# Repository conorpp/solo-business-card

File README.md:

# solo-business-card
A flex PCB business card that also works as a Solo

# BOM

|  Ref | value  | type  | package  | quantity  | Required? |
|---|---|---|---|---|--|
| C1-C9,C11  | 4.7u  | capacitor  | 0402  | 10  | yes |
| C10,C12  | \* xx, yy  | C0G capacitor  | 0402  | 10  | yes |
|  ST1 | STM32L432KU  |  Microcontroller | QFN32  | 1  |yes |
| N1  | AS3956-ATDM-S4  | NFC IC (SPI version)  | MLPD 3x3  | 1  |  yes |
|  R1 | 500R  | resistor  | 0402  | 1  |  no |
|  L1 | CL-505S-X-SD-T  | RGB LED  | 0606  | 1  |  no |

\* C10 and C12 are tunning capacitors connected in parallel.  I have not yet measured what the nominal value for them should be, but will be somewhere around 45pF.

# Assembly instructions

Assemble BOM on badge. 

# Programming

Connect programmer to debug port.  Connector uses the following cable.

http://www.tag-connect.com/TC2030-CTX-NL

Connect cable to an ARM debugger/programmer.  And program one of the "bundle" builds from the latest Solo release.

https://github.com/solokeys/solo/releases

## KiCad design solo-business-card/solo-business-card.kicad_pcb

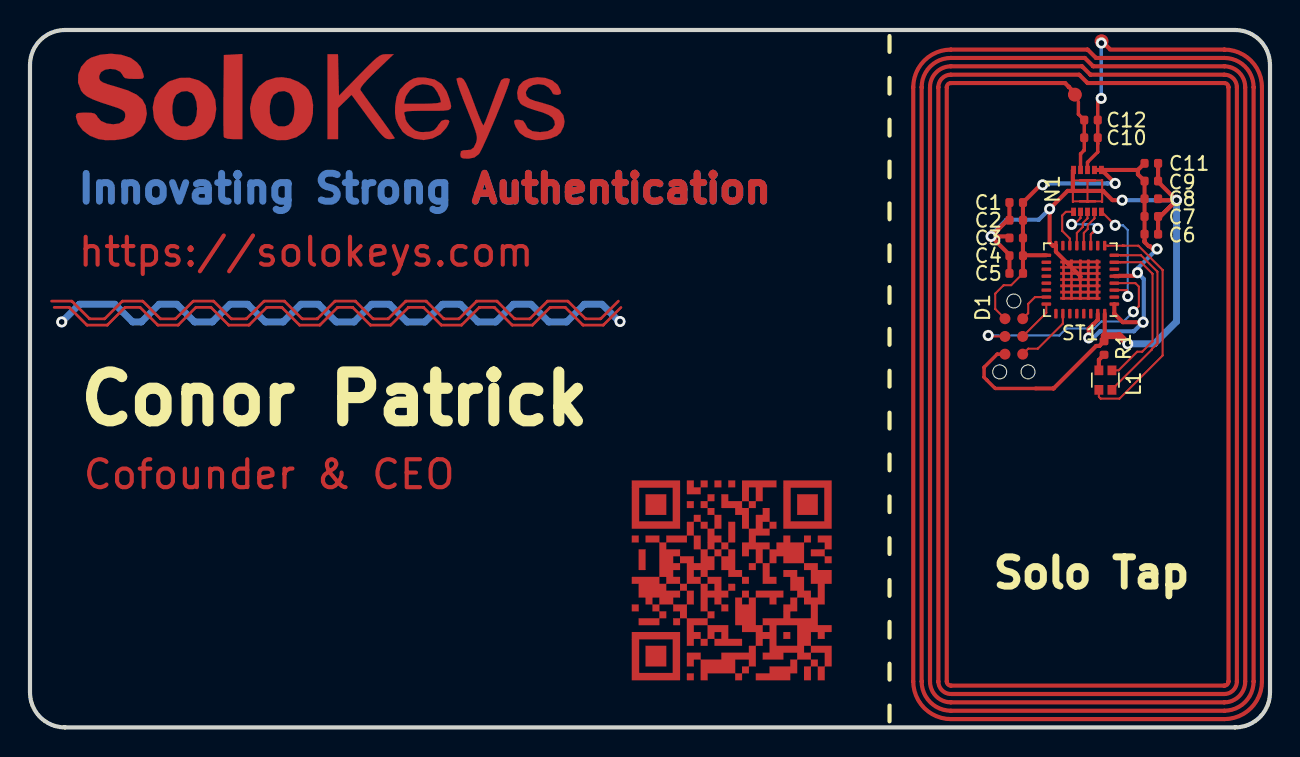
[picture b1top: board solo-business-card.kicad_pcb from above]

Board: 2 copper layers, 88.9 x 50.0 mm, 18 parts (0 on the bottom side), 17 nets.

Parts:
AE1: Antenna_Loop; NFC_CLASS_4
C1, C2, C3, C4, C5, C6, C7, C8, C9, C11: 4.7u; C_0402_1005Metric
C10: xx; C_0402_1005Metric
C12: yy; C_0402_1005Metric
D1: ARM_DEBUG; TC2030-IDC-NL
L1: RGB_1x1-CL-505S-S-SD-T; RGB_LED_606
N1: AMS3956; MLPD3X3
R1: 500; R_0402_1005Metric
ST1: STM32L4; QFN-32-1EP_5x5mm_P0.5mm_EP3.1x3.1mm

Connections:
+3V3: C1.2, C2.2, C3.2, C4.2, C5.2, C6.1, C7.1, C8.1, C9.1, C11.1, D1.1, N1.1, N1.2, ST1.1, ST1.5, ST1.17, ST1.31
/AMS_IRQ: N1.10, ST1.3
/nRESET: D1.3, ST1.4
GNDREF: C1.1, C2.1, C3.1, C4.1, C5.1, C6.2, C7.2, C8.2, C9.2, C11.2, D1.5, N1.5, N1.EXP, R1.1, ST1.16, ST1.32, ST1.EXP
unnamed: AE1.1, C10.1, C12.1, N1.4
unnamed: AE1.2, C10.2, C12.2, N1.3
unnamed: D1.2, ST1.23
unnamed: D1.4, ST1.24
unnamed: D1.6, ST1.26
unnamed: L1.1, ST1.9
unnamed: L1.2, ST1.8
unnamed: L1.3, ST1.7
unnamed: L1.4, R1.2
unnamed: N1.6, ST1.14
unnamed: N1.7, ST1.11
unnamed: N1.8, ST1.13
unnamed: N1.9, ST1.12

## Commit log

2019-11-13 more manufactureable
